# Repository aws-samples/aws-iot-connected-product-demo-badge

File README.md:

# AWS IoT - Connected Product - Demo Badge

## Workshop

The Demo Badge device was built for this hands-on workshop at re:Invent 2023 and future events:

https://catalog.workshops.aws/aws-iot-connected-product-demo-badge

Rendering of front and backside of the Demo Badge:

## Hardware

See the [Hardware README](./hardware/README.md) file.

### Where to buy?

Seeed Studio manufactured the devices for re:Invent 2023.

You can pre-order devices directly from the Seeed Studio online store [product listing for the Demo Badge](https://www.seeedstudio.com/AWS-IoT-Connected-Product-p-5844.html).

If you are interesting in customizing the Demo Badge for your own product design, please reach out to fusion@seeed.io directly, and tell them about the Demo Badge device!

## Firmware

See the [Firmware README](./firmware/README.md) file.

## Cloud Infrastructure with CDK

See the [CDK](./cloud-infrastructure/cdk/) folder.

## Security

See [CONTRIBUTING](CONTRIBUTING.md#security-issue-notifications) for more information.

## License

This project is licensed under the MIT-0 License, except files explicitly marked under different license. See the LICENSE file.

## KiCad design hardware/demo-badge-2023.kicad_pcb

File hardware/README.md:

# AWS IoT - Connected Product - Demo Badge 2023

This device was designed and created for a [hands-on workshop at re:Invent 2023](https://catalog.workshops.aws/aws-iot-connected-product-demo-badge).

The Demo Badge features an nRF52840 microcontroller, an Espressif ESP32-C3-MINI-1-A AWS IoT ExpressLink module, various sensors, buttons, RGB LEDs, and a color display.

## Schematic

The schematic for the Demo Badge is available as KiCAD 7 project. You can access a [PDF version of the schematic here](./snapshot/demo-badge-2023-schematic.pdf).

## PCB Layout

The PCB layout for the Demo Badge is available as KiCAD 7 project, including all footprints (publicly available ones, and custom ones).

You can access the [production Gerber files here](./snapshot/gerbers/).

## License

This hardware design is licensed under the MIT-0 License. Imported footprints and 3D models might contain different licenses.

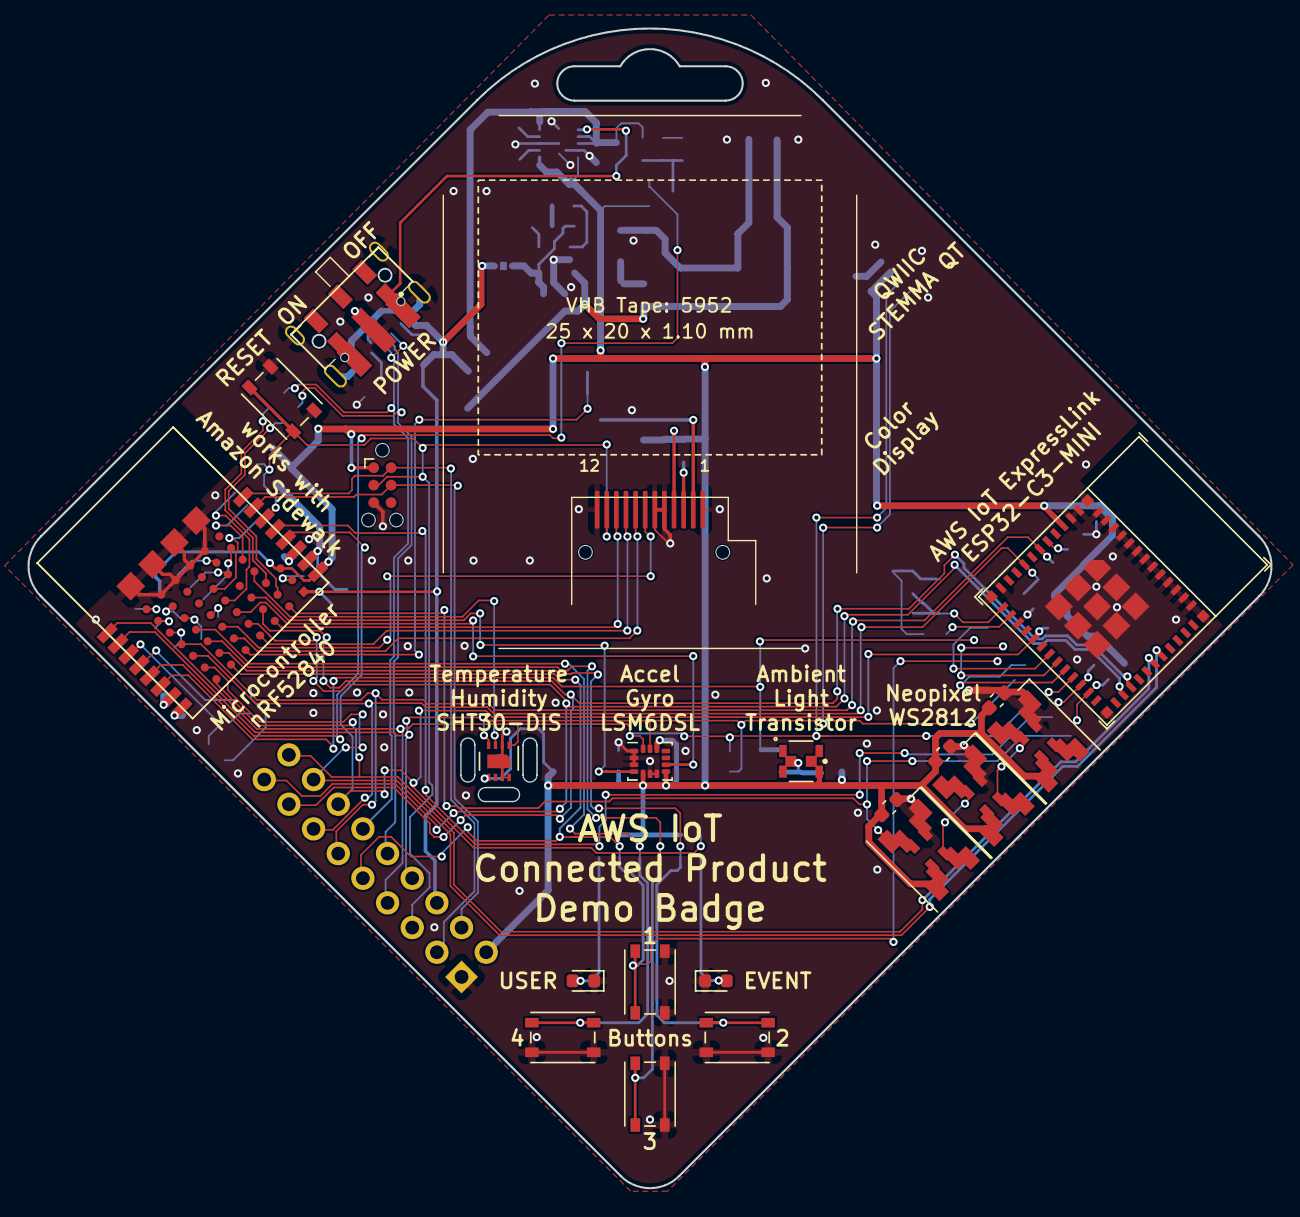
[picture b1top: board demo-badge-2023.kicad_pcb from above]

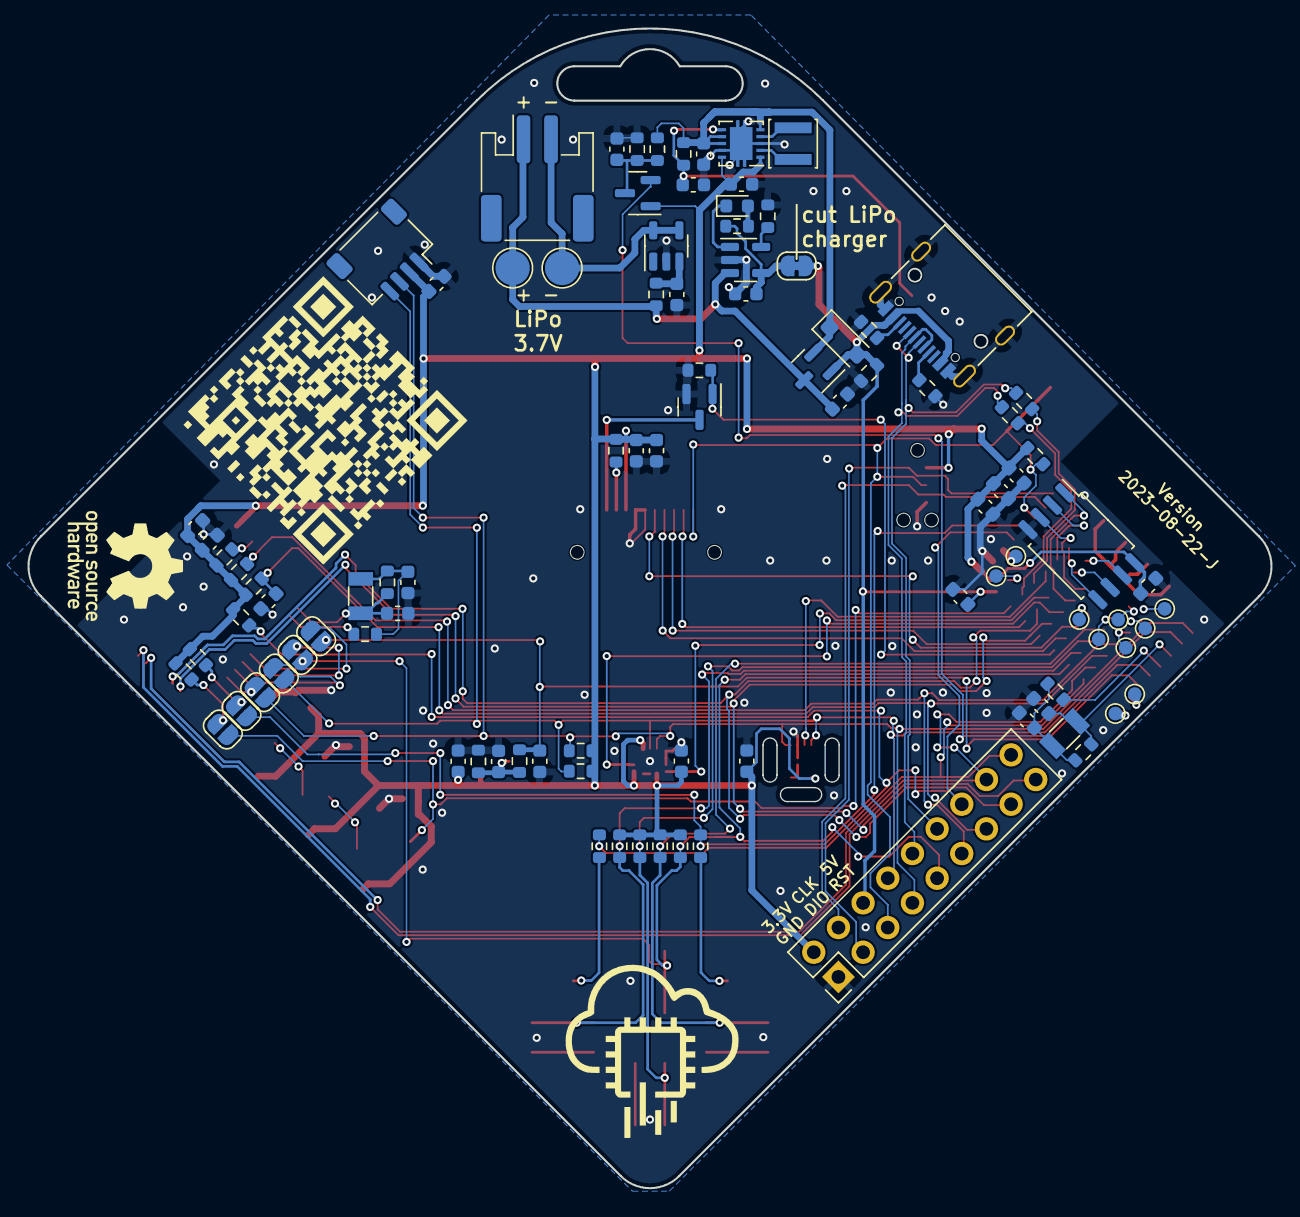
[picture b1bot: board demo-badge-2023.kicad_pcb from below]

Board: 2 copper layers, 90.5 x 84.4 mm, 119 parts (96 on the bottom side), 85 nets.

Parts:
A1: ALS-PT19-315C/L177/TR8; ALS-PT19-315C_L177_TR8
C1, C2, C3, C10, C14, C18, C20, C22, C41: 100nF; C_0603_1608Metric
C4, C5, C6, C11, C15, C17, C21, C35: 1uF; C_0603_1608Metric
C7, C19, C28, C32, C33: 10uF; C_0603_1608Metric
C8, C30, C31, C36: 4.7uF; C_0603_1608Metric
C29, C34, C39, C40: 27pF; C_0603_1608Metric
D1, D2, D3: WS2812B; SK6812-multi
D4, D5, D6: Green LED; LED_0603_1608Metric
D7: 20V 350mV@1A; D_SOD-123F
J1: TagConnect_TC2030-NL; Tag-Connect_TC2030-IDC-NL_2x03_P1.27mm_Vertical
J2: USB_C_Receptacle_USB2.0; USB_C_Receptacle_Palconn_UTC16-G
J3: JST SM04B-SRSS-TB; JST_SH_SM04B-SRSS-TB_1x04-1MP_P1.00mm_Horizontal
J6: DNP; PinHeader_2x09_P2.54mm_Vertical
J7: JST S2B-PH-SM4-TB; JST_PH_S2B-PH-SM4-TB_1x02-1MP_P2.00mm_Horizontal
JP1: SolderJumper_2_Bridged; SolderJumper-2_P1.3mm_Bridged_RoundedPad1.0x1.5mm
JP10, JP11, JP12, JP13, JP14, JP15: SolderJumper_2_Open; SolderJumper-2_P1.3mm_Open_RoundedPad1.0x1.5mm
L1: 2.2uH; L_Changjiang_FNR3015S
NFC1, NFC2: TestPoint; TestPoint_Pad_D1.0mm
Q1, Q3: 2N7002; SOT-23
Q2: DMG2305UX-7; SOT-23
R1: 1M; R_0603_1608Metric
R2: 750k; R_0603_1608Metric
R3, R4: 27; R_0603_1608Metric
R5, R7, R9, R10, R11, R12, R13, R14, R15, R18, R19, R20, R31, R37, R50: 10k; R_0603_1608Metric
R6: 7.5; R_0603_1608Metric
R8, R33, R52: 1k; R_0603_1608Metric
R16, R17, R34, R49: 100; R_0603_1608Metric
R22, R23, R29, R35, R36: 5k1; R_0603_1608Metric
R32, R51: DNP; R_0603_1608Metric
SW1, SW2, SW3, SW4, SW5: PTS815
SW7: JS202011JAQN
SW8: JS102011SAQN
TP1, TP2, TP3, TP4, TP5, TP8, TP9, TP11: TestPoint; TestPoint_Pad_D1.0mm
TP6, TP7: TestPoint; TestPoint_Pad_D2.5mm
U1: SHT30-DIS; Sensirion_DFN-8-1EP_2.5x2.5mm_P0.5mm_EP1.1x1.7mm
U4: BT840; Fanstel-BT840
U5: LSM6DSLTR; LGA-14_3x2.5mm_P0.5mm_LayoutBorder3x4y
U6: ESP32-C3-MINI-1-N4-A; ESP32-C3-MINI-1
U7: DNP; IN-S32GTLS
U9: TPS63001DRCR; Texas_DRC0010J
U10: TP4054; SOT-23-5
U12: BRCL3130ME; SOT-23-5
U13: ER-TFT1.69-2
U14: W25Q128JVSIQ; SOIC-8_5.23x5.23mm_P1.27mm
Y1, Y3: 32.768kHz 12.5pF; Crystal_SMD_3215-2Pin_3.2x1.5mm

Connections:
3V3_EN: C28.2, R31.2, SW7.1 (A), SW8.1, U9.6 (EN)
+3.3V: A1.1, C1.2, C2.2, C3.2, C4.2, C5.2, C6.2, C7.2, C10.2, C11.2, C18.2, C19.2, C22.2, C32.2, C35.2, C36.2, C41.2, D1.3 (VDD), D2.3 (VDD), D3.3 (VDD), J1.1 (VCC), J3.2, J6.2, Q1.1 (G), R6.2, R9.2, R10.2, R11.2, R12.2, R13.2, R14.2, R15.2, R18.2, R19.2, R20.2, R35.2, R36.2, R37.2, U1.5 (VDD), U4.P$9 (VDD), U4.P$F4 (F4/VDDH), U5.5 (VDDIO), U5.8 (VDD), U5.12 (CS), U6.3 (3V3), U7.3, U7.4, U9.1 (VOUT), U9.10 (FB), U13.4 (VDD), U14.8 (VCC)
/ExpressLink/XTAL_N: R33.2, U6.13 (GPIO1/ADC1_CH1/XTAL_32K_N)
/ExpressLink/XTAL_P: C29.1, R32.2, U6.12 (GPIO0/ADC1_CH0/XTAL_32K_P), Y1.2
/Power/VBUS_CHARGE: C31.2, JP1.2 (B), R34.2, U10.4 (V_{DD})
/nrf52840/QSPI_CLK: U4.P$D2 (D2/NC), U14.6 (CLK)
/nrf52840/QSPI_SDIO_DATA0: U4.P$E1 (E1/P20), U14.5 (DI(IO0))
/nrf52840/QSPI_SDIO_DATA1: U4.P$E2 (E2/P21), U14.2 (DO(IO1))
/nrf52840/QSPI_SDIO_DATA2: U4.P$C2 (C2/P22), U14.3 (IO2)
/nrf52840/QSPI_SDIO_DATA3: U4.P$D1 (D1/P23), U14.7 (IO3)
/nrf52840/QSPI_SS: U4.P$C3 (C3/NC), U14.1 (~CS)
/nrf52840/SPI_MISO: TP11.1, U4.P$B3 (B3/P31)
/nrf52840/XTAL_N: R52.2, U4.P$4 (P01/XL2)
/nrf52840/XTAL_P: C39.1, R51.2, U4.P$3 (P00/XL1), Y3.2
AMBIENT_LIGHT: C15.2, JP12.2 (B), R7.2, U4.P$6 (P03/AIN1)
BACKLIGHT: Q3.1 (G), R5.2, U4.P$B6 (B6/P103)
BAT_RECHARGE_NEG: J7.2, TP7.1, U12.4 (VM), U12.5 (VM)
BAT_RECHARGE_POS: C30.2, J7.1, Q2.3 (D), R49.1, TP6.1, U10.3 (V_{BAT})
BAT_VOLTAGE_MONITOR: Q1.2 (S), U4.P$5 (P02/AIN0)
BTN1: J6.9, JP13.2 (B), R12.1, SW1.1, U4.P$A6 (A6/P108)
BTN2: R13.1, SW2.1, U4.P$A5 (A5/P07)
BTN3: R14.1, SW3.1, U4.P$A4 (A4/P05)
BTN4: R15.1, SW4.1, U4.P$A3 (A3/P04)
CHARGE: D6.1 (K), U10.1 (STAT)
DISPLAY_DC: U4.P$B4 (B4/NC), U13.7 (D/C)
EL_DBG_RXD: J6.18, U4.P$Z6 (Z6/P106), U6.30 (GPIO20/U0RXD)
EL_DBG_TXD: J6.16, U4.P$Z5 (Z5/P110), U6.31 (GPIO21/U0TXD)
EL_EVENT: J6.14, R9.1, R17.2, U4.P$12 (P18), U6.16 (GPIO10)
EL_RESET: C14.1, J6.13, R18.1, U4.P$Z4 (Z4/P115), U6.8 (EN/CHIP_PU)
EL_RXD: J6.17, U4.P$C5 (C5/P12), U6.26 (GPIO18/USB_D-)
EL_TXD: J6.15, U4.P$D5 (D5/P11), U6.27 (GPIO19/USB_D+)
EL_WAKE: J6.11, R10.1, U4.P$Z3 (Z3/P114), U6.6 (GPIO3/ADC1_CH3)
ESP32_FUTURE_USE_GPIO4: JP12.1 (A), U6.18 (GPIO4/ADC1_CH4)
ESP32_FUTURE_USE_GPIO5: JP13.1 (A), U6.19 (GPIO5/ADC2_CH0)
ESP32_FUTURE_USE_GPIO6: JP10.1 (A), U6.20 (GPIO6)
ESP32_FUTURE_USE_GPIO7: JP11.1 (A), U6.21 (GPIO7)
ESP32_FUTURE_USE_GPIO8: JP14.1 (A), R20.1, U6.22 (GPIO8)
ESP32_FUTURE_USE_GPIO9: JP15.1 (A), R19.1, U6.23 (GPIO9)
GND: C1.1, C2.1, C3.1, C4.1, C5.1, C6.1, C7.1, C8.1, C10.1, C11.1, C14.2, C15.1, C17.1, C18.1, C19.1, C20.1, C21.1, C22.1, C28.1, C29.2, C30.1, C31.1, C32.1, C33.1, C34.2, C35.1, C36.1, C39.2, C40.2, C41.1, D1.1 (VSS), D2.1 (VSS), D3.1 (VSS), D4.1 (K), D5.1 (K), J1.5 (GND), J2.A1 (GND), J2.A12 (GND), J2.B1 (GND), J2.B12 (GND), J2.S1 (SHIELD), J3.1, J6.1, Q3.2 (S), R2.2, R5.1, R8.1, R22.1, R23.1, R29.2, R50.2, SW1.2, SW2.2, SW3.2, SW4.2, SW5.2, SW7.2 (B), SW8.2, U1.2 (ADDR), U1.7 (R), U1.8 (VSS), U1.9 (VSS), U4.P$10 (GND), U4.P$A0 (A0/VSS1), U4.P$B0 (B0/VSS2), U4.P$C0 (C0/VSS3), U4.P$D0 (D0/VSS4), U4.P$F0 (F0/GND), U4.P$F1 (F1/GND), U4.P$F2 (F2/GND), U4.P$F3 (F3/GND), U5.1 (SDO/SA0), U5.2 (SDX), U5.3 (SCX), U5.6 (GND), U5.7 (GND), U6.1 (GND), U6.2 (GND), U6.11 (GND), U6.14 (GND), U6.36 (GND), U9.3 (PGND), U9.9 (GND), U9.11 (PGND), U10.2 (V_{SS}), U12.2 (GND), U13.1 (GND), U13.5 (GND), U13.6 (GND), U13.12 (GND), U14.4 (GND)
I2C_SCL: J3.4, J6.8, JP10.2 (B), R35.1, U1.4 (SCL), U4.P$2 (P27/SCL), U5.13 (SCL)
I2C_SDA: J3.3, J6.7, JP11.2 (B), R36.1, U1.1 (SDA), U4.P$1 (P26/SDA), U5.14 (SDA)
LEDA: R6.1, U13.3 (LEDA)
LEDK: Q3.3 (D), U13.2 (LEDK)
LSM6DSL_INT1: U4.P$D4 (D4/P14), U5.4 (INT1)
LSM6DSL_INT2: U4.P$C4 (C4/P15), U5.9 (INT2)
NEOPIXEL_DATA: D1.2 (DIN), JP15.2 (B), U4.P$E6 (E6/P12)
unnamed: A1.2, C17.2, R7.1, R8.2, U7.1, U7.2
unnamed: C34.1, R32.1, R33.1, Y1.1
unnamed: C40.1, R51.1, R52.1, Y3.1
unnamed: D1.4 (DOUT), D2.2 (DIN)
unnamed: D2.4 (DOUT), D3.2 (DIN)
unnamed: D4.2 (A), R16.1
unnamed: D5.2 (A), R17.1
unnamed: D6.2 (A), R34.1
unnamed: J2.A5 (CC1), R22.2
unnamed: J2.B5 (CC2), R23.2
unnamed: C20.2, Q1.3 (D), R1.2, R2.1
unnamed: TP8.1, U4.P$A1 (A1/P28)
unnamed: TP9.1, U4.P$A2 (A2/P29)
unnamed: R3.2, U4.P$E4 (E4/D+)
unnamed: R4.2, U4.P$E5 (E5/D-)
unnamed: TP2.1, U4.P$F5 (F5/DCCH)
unnamed: NFC1.1, U4.P$7 (P09)
unnamed: NFC2.1, U4.P$8 (P10)
unnamed: TP1.1, U4.P$11 (P13)
unnamed: TP3.1, U4.P$Z0 (Z0/P111)
unnamed: TP4.1, U4.P$Z1 (Z1/P112)
unnamed: TP5.1, U4.P$Z2 (Z2/P113)
unnamed: R11.1, U6.5 (GPIO2/ADC1_CH2)
unnamed: L1.1, U9.4 (L1)
unnamed: L1.2, U9.2 (L2)
unnamed: R29.1, U10.5 (PROG)
unnamed: C21.2, R49.2, U12.3 (VDD)
RESET: J1.3 (~RESET), J6.5, R37.1, SW5.1, U4.P$14 (P21/RESET), U13.11 (RESET)
SHT30_ALERT: U1.3 (ALERT), U4.P$E3 (E3/P109)
SPI_CS: U4.P$B5 (B5/P08), U13.8 (CS)
SPI_MOSI: U4.P$D6 (D6/P105), U13.10 (SDA(MOSI))
SPI_SCK: U4.P$C6 (C6/P104), U13.9 (SCL(SCK))
SWCLK: J1.4 (SWCLK), J6.4, U4.P$15 (SWCLK)
SWDIO: J1.2 (SWDIO), J6.3, U4.P$16 (SWDIO)
USB_D+: J2.A6 (D+), J2.B6 (D+), J6.12, R3.1
USB_D-: J2.A7 (D-), J2.B7 (D-), J6.10, R4.1
USER_LED: JP14.2 (B), R16.2, U4.P$13 (P20)
VBUS: C8.2, D7.2 (A), J2.A4 (VBUS), J2.A9 (VBUS), J2.B4 (VBUS), J2.B9 (VBUS), J6.6, JP1.1 (A), Q2.1 (G), R50.1, U4.P$F6 (F6/VBUS)
VSYS: C33.2, D7.1 (K), Q2.2 (S), R1.1, R31.1, U9.5 (VIN), U9.7 (PS/SYNC), U9.8 (VINA)

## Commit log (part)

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2023-11-24 This is where it all begins...
2023-11-28 add Seeed Studio product listing
2023-12-06 Bump vite from 4.5.0 to 4.5.1 in /companion_web_app
    Bumps [vite](https://github.com/vitejs/vite/tree/HEAD/packages/vite) from 4.5.0 to 4.5.1.
    - [Release notes](https://github.com/vitejs/vite/releases)
    - [Changelog](https://github.com/vitejs/vite/blob/v4.5.1/packages/vite/CHANGELOG.md)
    - [Commits](https://github.com/vitejs/vite/commits/v4.5.1/packages/vite)
    ---
    updated-dependencies:
2024-01-11 Bump follow-redirects from 1.15.3 to 1.15.4 in /companion_web_app
    Bumps [follow-redirects](https://github.com/follow-redirects/follow-redirects) from 1.15.3 to 1.15.4.
    - [Release notes](https://github.com/follow-redirects/follow-redirects/releases)
    - [Commits](https://github.com/follow-redirects/follow-redirects/compare/v1.15.3...v1.15.4)
    ---
    updated-dependencies:
    - dependency-name: follow-redirects
2024-01-20 Bump vite from 4.5.1 to 4.5.2 in /companion_web_app
    Bumps [vite](https://github.com/vitejs/vite/tree/HEAD/packages/vite) from 4.5.1 to 4.5.2.
    - [Release notes](https://github.com/vitejs/vite/releases)
    - [Changelog](https://github.com/vitejs/vite/blob/v4.5.2/packages/vite/CHANGELOG.md)
    - [Commits](https://github.com/vitejs/vite/commits/v4.5.2/packages/vite)
    ---
    updated-dependencies:
2024-01-31 flashing instructions++
2024-01-31 display: use existing function
2024-01-31 display: wrap async lvgl handler to different thread
2024-01-31 self-test: expresslink EL_EVENT reset fix
2024-01-31 improve first-boot experience and checks
2024-03-16 build(deps): bump follow-redirects in /companion_web_app
    Bumps [follow-redirects](https://github.com/follow-redirects/follow-redirects) from 1.15.4 to 1.15.6.
    - [Release notes](https://github.com/follow-redirects/follow-redirects/releases)
    - [Commits](https://github.com/follow-redirects/follow-redirects/compare/v1.15.4...v1.15.6)
    ---
    updated-dependencies:
    - dependency-name: follow-redirects
2024-04-04 build(deps-dev): bump vite from 4.5.2 to 4.5.3 in /companion_web_app
    Bumps [vite](https://github.com/vitejs/vite/tree/HEAD/packages/vite) from 4.5.2 to 4.5.3.
    - [Release notes](https://github.com/vitejs/vite/releases)
    - [Changelog](https://github.com/vitejs/vite/blob/v4.5.3/packages/vite/CHANGELOG.md)
    - [Commits](https://github.com/vitejs/vite/commits/v4.5.3/packages/vite)
    ---
    updated-dependencies:
2024-06-05 add product photo and rendering images
2024-06-18 build(deps): bump ws from 7.5.9 to 7.5.10 in /companion_web_app
    Bumps [ws](https://github.com/websockets/ws) from 7.5.9 to 7.5.10.
    - [Release notes](https://github.com/websockets/ws/releases)
    - [Commits](https://github.com/websockets/ws/compare/7.5.9...7.5.10)
    ---
    updated-dependencies:
    - dependency-name: ws
2024-06-18 build(deps-dev): bump braces from 3.0.2 to 3.0.3 in /companion_web_app
    Bumps [braces](https://github.com/micromatch/braces) from 3.0.2 to 3.0.3.
    - [Changelog](https://github.com/micromatch/braces/blob/master/CHANGELOG.md)
    - [Commits](https://github.com/micromatch/braces/compare/3.0.2...3.0.3)
    ---
    updated-dependencies:
    - dependency-name: braces
2024-08-09 bump dependencies
2024-08-19 build(deps): bump axios from 1.6.0 to 1.7.4 in /companion_web_app
    Bumps [axios](https://github.com/axios/axios) from 1.6.0 to 1.7.4.
    - [Release notes](https://github.com/axios/axios/releases)
    - [Changelog](https://github.com/axios/axios/blob/v1.x/CHANGELOG.md)
    - [Commits](https://github.com/axios/axios/compare/v1.6.0...v1.7.4)
    ---
    updated-dependencies:
2024-09-18 build(deps-dev): bump vite from 4.5.3 to 4.5.5 in /companion_web_app
    Bumps [vite](https://github.com/vitejs/vite/tree/HEAD/packages/vite) from 4.5.3 to 4.5.5.
    - [Release notes](https://github.com/vitejs/vite/releases)
    - [Changelog](https://github.com/vitejs/vite/blob/v4.5.5/packages/vite/CHANGELOG.md)
    - [Commits](https://github.com/vitejs/vite/commits/v4.5.5/packages/vite)
    ---
    updated-dependencies:
2024-09-26 build(deps-dev): bump rollup from 3.29.4 to 3.29.5 in /companion_web_app
    Bumps [rollup](https://github.com/rollup/rollup) from 3.29.4 to 3.29.5.
    - [Release notes](https://github.com/rollup/rollup/releases)
    - [Changelog](https://github.com/rollup/rollup/blob/master/CHANGELOG.md)
    - [Commits](https://github.com/rollup/rollup/compare/v3.29.4...v3.29.5)
    ---
    updated-dependencies:
2025-06-12 build(deps): bump brace-expansion in /companion_web_app
    Bumps [brace-expansion](https://github.com/juliangruber/brace-expansion) from 1.1.11 to 1.1.12.
    - [Release notes](https://github.com/juliangruber/brace-expansion/releases)
    - [Commits](https://github.com/juliangruber/brace-expansion/compare/1.1.11...v1.1.12)
    ---
    updated-dependencies:
    - dependency-name: brace-expansion
2025-06-12 build(deps): bump axios from 1.7.4 to 1.9.0 in /companion_web_app
    Bumps [axios](https://github.com/axios/axios) from 1.7.4 to 1.9.0.
    - [Release notes](https://github.com/axios/axios/releases)
    - [Changelog](https://github.com/axios/axios/blob/v1.x/CHANGELOG.md)
    - [Commits](https://github.com/axios/axios/compare/v1.7.4...v1.9.0)
    ---
    updated-dependencies:
2025-06-12 build(deps-dev): bump vite from 4.5.5 to 4.5.14 in /companion_web_app
    Bumps [vite](https://github.com/vitejs/vite/tree/HEAD/packages/vite) from 4.5.5 to 4.5.14.
    - [Release notes](https://github.com/vitejs/vite/releases)
    - [Changelog](https://github.com/vitejs/vite/blob/v4.5.14/packages/vite/CHANGELOG.md)
    - [Commits](https://github.com/vitejs/vite/commits/v4.5.14/packages/vite)
    ---
    updated-dependencies:
2025-06-12 build(deps): bump esbuild and vite in /companion_web_app
    Bumps [esbuild](https://github.com/evanw/esbuild) to 0.25.5 and updates ancestor dependency [vite](https://github.com/vitejs/vite/tree/HEAD/packages/vite). These dependencies need to be updated toget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
    Updates `esbuild` from 0.18.20 to 0.25.5
    - [Release notes](https://github.com/evanw/esbuild/releases)
    - [Changelog](https://github.com/evanw/esbuild/blob/main/CHANGELOG-2023.md)
    - [Commits](https://github.com/evanw/esbuild/compare/v0.18.20...v0.25.5)
    Updates `vite` from 4.5.5 to 6.3.5
2026-03-25 build(deps): bump picomatch in /companion_web_app
    Bumps and [picomatch](https://github.com/micromatch/picomatch). These dependencies needed to be updated together.
    Updates `picomatch` from 2.3.1 to 2.3.2
    - [Release notes](https://github.com/micromatch/picomatch/releases)
    - [Changelog](https://github.com/micromatch/picomatch/blob/master/CHANGELOG.md)
    - [Commits](https://github.com/micromatch/picomatch/compare/2.3.1...2.3.2)
    Updates `picomatch` from 4.0.2 to 4.0.4
2026-04-07 build(deps-dev): bump vite from 6.4.1 to 6.4.2 in /companion_web_app
    Bumps [vite](https://github.com/vitejs/vite/tree/HEAD/packages/vite) from 6.4.1 to 6.4.2.
    - [Release notes](https://github.com/vitejs/vite/releases)
    - [Changelog](https://github.com/vitejs/vite/blob/v6.4.2/packages/vite/CHANGELOG.md)
    - [Commits](https://github.com/vitejs/vite/commits/v6.4.2/packages/vite)
    ---
    updated-dependencies:
2026-04-07 build(deps): bump brace-expansion in /companion_web_app
    Bumps [brace-expansion](https://github.com/juliangruber/brace-expansion) from 1.1.12 to 1.1.13.
    - [Release notes](https://github.com/juliangruber/brace-expansion/releases)
    - [Commits](https://github.com/juliangruber/brace-expansion/compare/v1.1.12...v1.1.13)
    ---
    updated-dependencies:
    - dependency-name: brace-expansion
2026-04-12 build(deps): bump axios from 1.13.5 to 1.15.0 in /companion_web_app
    Bumps [axios](https://github.com/axios/axios) from 1.13.5 to 1.15.0.
    - [Release notes](https://github.com/axios/axios/releases)
    - [Changelog](https://github.com/axios/axios/blob/v1.x/CHANGELOG.md)
    - [Commits](https://github.com/axios/axios/compare/v1.13.5...v1.15.0)
    ---
    updated-dependencies:
2026-04-22 build(deps): bump uuid, @aws-sdk/client-iot, @aws-sdk/client-iot-data-plane, @aws-sdk/client-iot-wireless, @aws-sdk/client-lambda, @aws-sdk/client-s3, @aws-sdk/credential-provider-cognito-identity an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
    Bumps [uuid](https://github.com/uuidjs/uuid), [@aws-sdk/client-iot](https://github.com/aws/aws-sdk-js-v3/tree/HEAD/clients/client-iot), [@aws-sdk/client-iot-data-plane](https://github.com/aws/aws-sdk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
2026-05-07 build(deps): bump ip-address from 10.1.0 to 10.2.0 in /companion_web_app
    Bumps [ip-address](https://github.com/beaugunderson/ip-address) from 10.1.0 to 10.2.0.
    - [Commits](https://github.com/beaugunderson/ip-address/commits)
    ---
    updated-dependencies:
    - dependency-name: ip-address
    dependency-version: 10.2.0
2026-05-07 build(deps): bump axios from 1.15.0 to 1.16.0 in /companion_web_app
    Bumps [axios](https://github.com/axios/axios) from 1.15.0 to 1.16.0.
    - [Release notes](https://github.com/axios/axios/releases)
    - [Changelog](https://github.com/axios/axios/blob/v1.x/CHANGELOG.md)
    - [Commits](https://github.com/axios/axios/compare/v1.15.0...v1.16.0)
    ---
    updated-dependencies:
2026-05-07 build(deps-dev): bump postcss from 8.5.5 to 8.5.14 in /companion_web_app
    Bumps [postcss](https://github.com/postcss/postcss) from 8.5.5 to 8.5.14.
    - [Release notes](https://github.com/postcss/postcss/releases)
    - [Changelog](https://github.com/postcss/postcss/blob/main/CHANGELOG.md)
    - [Commits](https://github.com/postcss/postcss/compare/8.5.5...8.5.14)
    ---
    updated-dependencies:
2026-05-07 build(deps): bump fast-xml-parser, @aws-sdk/xml-builder and @aws-sdk/client-sts
    Bumps [fast-xml-parser](https://github.com/NaturalIntelligence/fast-xml-parser) to 5.7.2 and updates ancestor dependencies [fast-xml-parser](https://github.com/NaturalIntelligence/fast-xml-parser), [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
    Updates `fast-xml-parser` from 5.5.8 to 5.7.2
    - [Release notes](https://github.com/NaturalIntelligence/fast-xml-parser/releases)
    - [Changelog](https://github.com/NaturalIntellig
2026-05-29 build(deps): bump ws from 8.19.0 to 8.21.0 in /companion_web_app
    Bumps [ws](https://github.com/websockets/ws) from 8.19.0 to 8.21.0.
    - [Release notes](https://github.com/websockets/ws/releases)
    - [Commits](https://github.com/websockets/ws/compare/8.19.0...8.21.0)
    ---
    updated-dependencies:
    - dependency-name: ws
2026-06-14 build(deps): bump esbuild and vite in /companion_web_app
    Removes [esbuild](https://github.com/evanw/esbuild). It's no longer used after updating ancestor dependency [vite](https://github.com/vitejs/vite/tree/HEAD/packages/vite). These dependencies need to 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
    Removes `esbuild`
    Updates `vite` from 6.4.2 to 8.0.16
    - [Release notes](https://github.com/vitejs/vite/releases)
    - [Changelog](https://github.com/vitejs/vite/blob/main/packages/vite/CHANGELOG.md)
    - [Commits](https://github.com/vitejs/vite/commits/v8.0.16/packages/vite)
2026-06-14 build(deps): bump js-cookie and amazon-cognito-identity-js
    Bumps [js-cookie](https://github.com/js-cookie/js-cookie) to 3.0.8 and updates ancestor dependency [amazon-cognito-identity-js](https://github.com/aws-amplify/amplify-js). These dependencies need to 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
    Updates `js-cookie` from 2.2.1 to 3.0.8
    - [Release notes](https://github.com/js-cookie/js-cookie/releases)
    - [Commits](https://github.com/js-cookie/js-cookie/compare/v2.2.1...v3.0.8)
    Updates `amazon-cognito-identity-js` from 6.3.6 to 6.3.17
    - [Release notes](https://github.com/aws-amplify/amplify-js/releases)
